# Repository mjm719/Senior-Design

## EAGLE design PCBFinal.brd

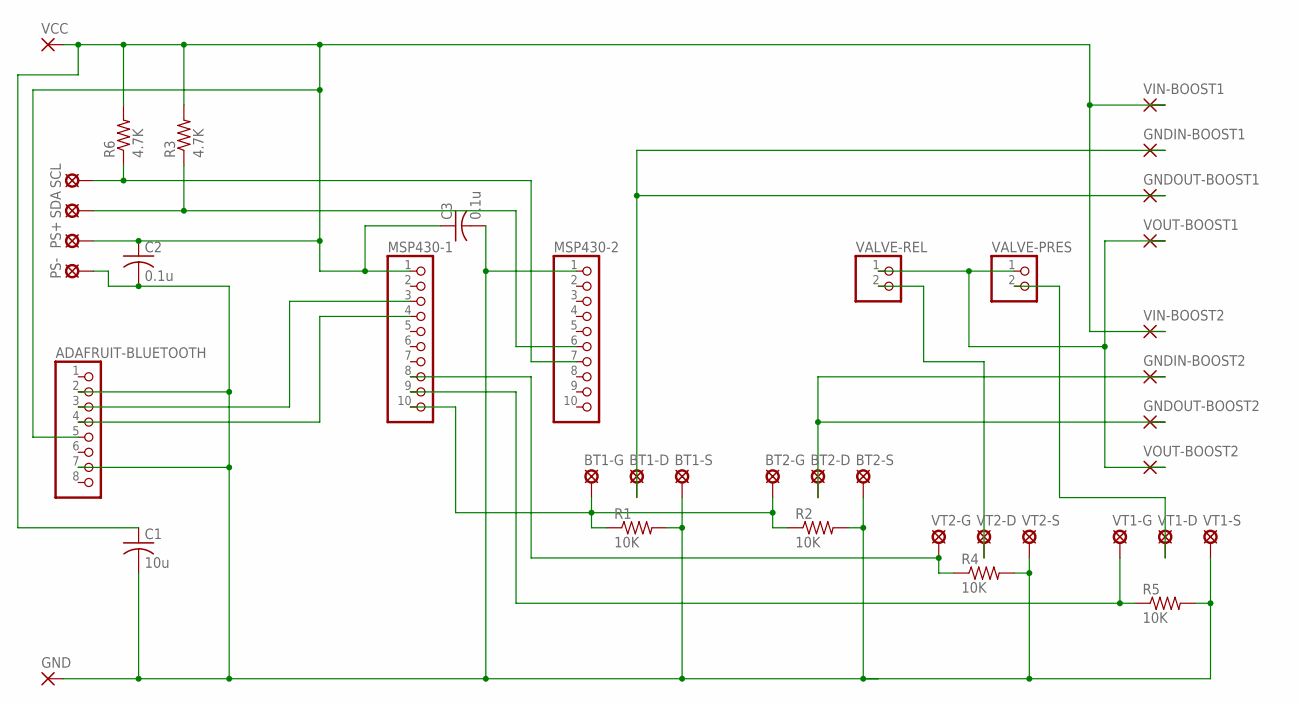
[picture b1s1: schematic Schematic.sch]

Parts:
ADAFRUIT-BLUETOOTH: PINHD-1X8; 1X08
BT1-D, BT1-G, BT1-S, BT2-D, BT2-G, BT2-S: LSP10
C1: 10u; C0805
C2, C3: 0.1u; C0805
GND: SMD5; SMD2,54-5,08
GNDIN-BOOST1, GNDIN-BOOST2: SMD5; SMD2,54-5,08
GNDOUT-BOOST1, GNDOUT-BOOST2: SMD5; SMD2,54-5,08
MSP430-1, MSP430-2: PINHD-1X10; 1X10
PS+: LSP10
PS-: LSP10
R1, R2, R4, R5: 10K; 0309/12
R3, R6: 4.7K; 0309/12
SCL: LSP10
SDA: LSP10
VALVE-PRES: PINHD-1X2; 1X02
VALVE-REL: PINHD-1X2; 1X02
VCC: SMD5; SMD2,54-5,08
VIN-BOOST1, VIN-BOOST2: SMD5; SMD2,54-5,08
VOUT-BOOST1, VOUT-BOOST2: SMD5; SMD2,54-5,08
VT1-D, VT1-G, VT1-S, VT2-D, VT2-G, VT2-S: LSP10

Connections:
unnamed: MSP430-2.7, R6.1, SCL.MP
unnamed: MSP430-2.6, R3.1, SDA.MP
unnamed 2: ADAFRUIT-BLUETOOTH.5, C1.1, C2.1, C3.1, MSP430-1.1, PS+.MP, R3.2, R6.2, VCC.1, VIN-BOOST1.1, VIN-BOOST2.1; also elsewhere on the board
unnamed: ADAFRUIT-BLUETOOTH.3, MSP430-1.3
unnamed: ADAFRUIT-BLUETOOTH.4, MSP430-1.4
unnamed: VALVE-PRES.1, VALVE-REL.1, VOUT-BOOST1.1, VOUT-BOOST2.1
unnamed 6: ADAFRUIT-BLUETOOTH.2, ADAFRUIT-BLUETOOTH.7, BT1-S.MP, BT2-S.MP, C1.2, C2.2, C3.2, GND.1, MSP430-2.1, PS-.MP, R1.2, R2.2, R4.2, R5.2, VT1-S.MP, VT2-S.MP; also elsewhere on the board
unnamed: MSP430-1.8, R4.1, VT2-G.MP
unnamed: BT1-G.MP, BT2-G.MP, MSP430-1.10, R1.1, R2.1
unnamed: MSP430-1.9, R5.1, VT1-G.MP
unnamed: VALVE-PRES.2, VT1-D.MP
unnamed: VALVE-REL.2, VT2-D.MP
unnamed: BT1-D.MP, GNDIN-BOOST1.1, GNDOUT-BOOST1.1
unnamed: BT2-D.MP, GNDIN-BOOST2.1, GNDOUT-BOOST2.1

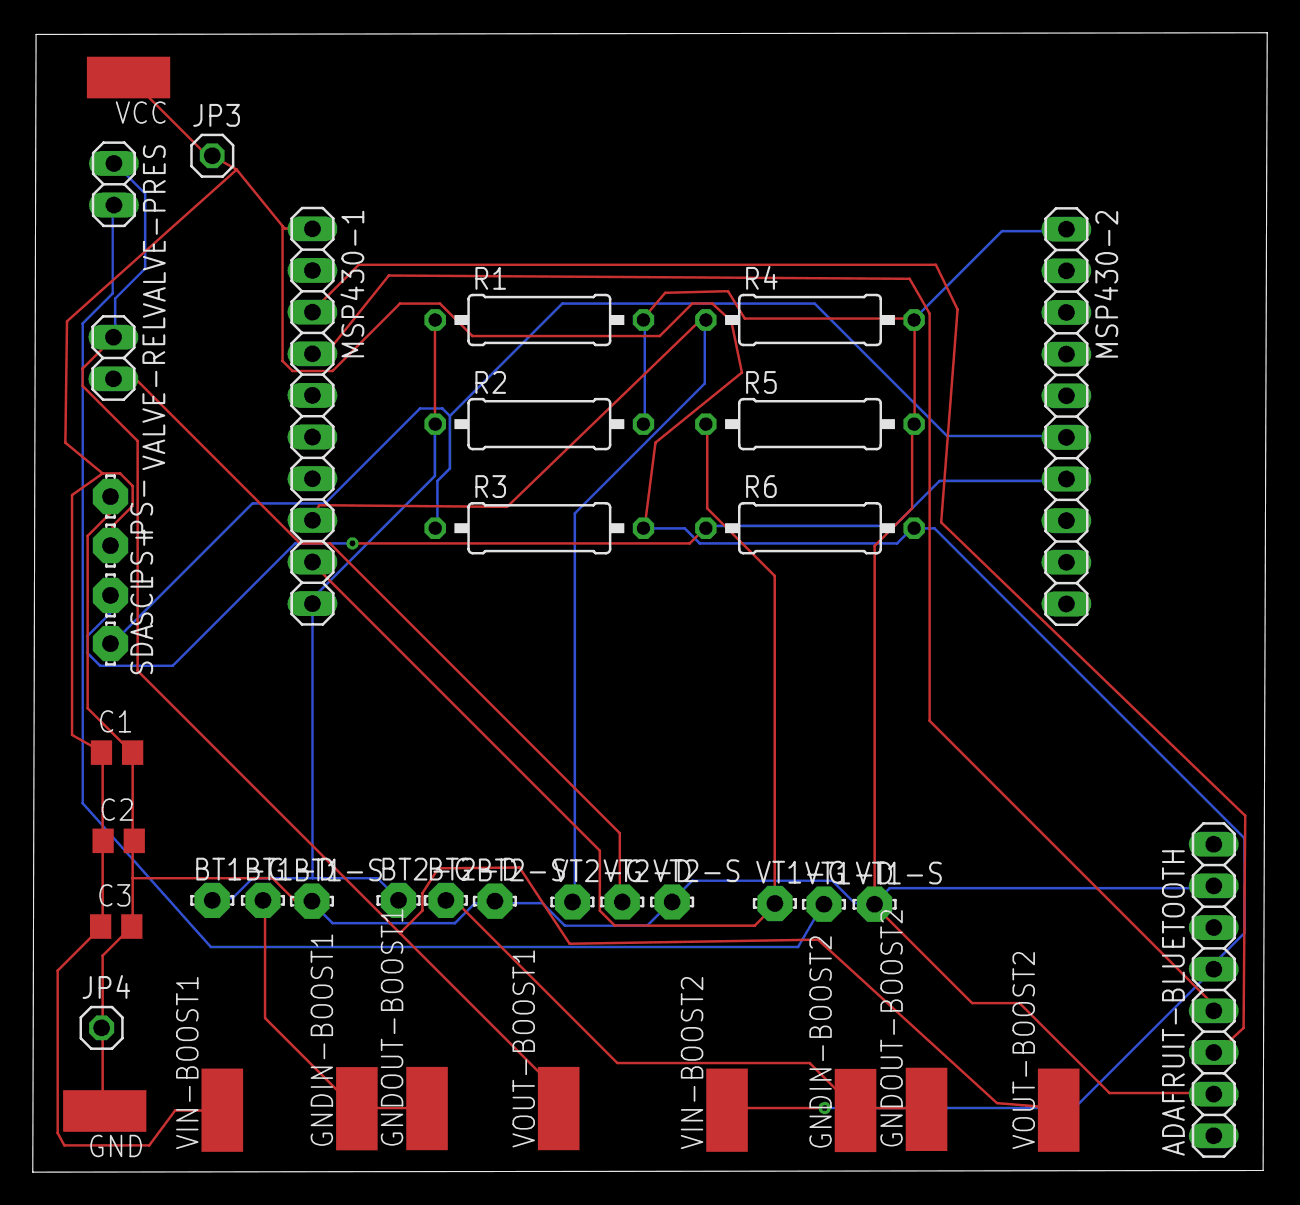
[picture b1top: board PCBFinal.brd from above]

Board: 2 copper layers, 75.3 x 69.5 mm, 42 parts (0 on the bottom side), 14 nets.

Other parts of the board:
JP3, JP4: 1X01

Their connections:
unnamed 2: JP3.1; also elsewhere on the board
unnamed 6: JP4.1; also elsewhere on the board

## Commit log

2016-12-15 Uploading Sample Code
    Creating Initial Folders
2016-12-15 MSP430 Document
    Extremely Useful document. Explains how to program the MSP430
2016-12-15 Document with Parts
    Not even close to finished. Just ideas I have for parts
2016-12-21 Adding MSP430 Pinout
    Not all will be connected. Excel sheet show on the microcontroller tab
    what our connections need to be
2016-12-21 Document for Bluetooth Specs
2016-12-21 Update
    Has link to battery I posted. Just to keep track of it so we don't lose
    it
2017-02-08 Parts Update
    Also Contains a few miscellaneous things
2017-02-13 Order Info
2017-03-04 Adding base case, working uart program for cc2650
2017-03-04 moving base case, working uart program for cc2650 to appropriate folder
2017-03-04 moved cc2650 uart code to bluetooth code folder
2017-03-04 New Order
2017-03-04 More Order Forms
2017-03-04 Working UART code
    Also has beginnings of the main program to be used
2017-03-08 adding test multi-byte uart
2017-03-08 Even More Part Orders
    $$$$$$$$
2017-03-09 MSP430 Code
    UART, Multi-Byte UART, I2C
2017-03-09 adding functional uart echo multi byte for cc2650
2017-03-29 Add files via upload
    Android Bluetooth Connectivity Source Code
2017-03-29 Rename MainActivity.cs to Android/BluetoothTestingv2/MainActivity.c
2017-03-29 Rename Android/BluetoothTestingv2/MainActivity.cs to Android/BPR/MainActivity.cs
2017-03-29 Rename Android/BluetoothTestingv2/MainActivity.c to Android/Bluetooth/MainActivity.cs
2017-03-29 Rename Android/BPR/MainActivity.cs to Android/Main/MainActivity.cs
2017-03-29 cleanup
2017-03-30 added bluetooth and main
2017-03-30 various cleanup
2017-03-30 added LE project
2017-03-31 BLE update
2017-03-31 added GATT connection
2017-04-01 Bluetooth Java Code
2017-04-03 update 4/3/17
2017-04-03 adding Project Zero (bluetooth example)
2017-04-03 Adding Project Zero stack
2017-04-03 adding Multibyte UART project
2017-04-03 added GATT server connection
2017-04-05 added permissions request at runtime
2017-04-06 added BLE characteristic read functionality
2017-04-06 added high level read/write functions
2017-04-06 various cleanup; added button control
2017-04-06 successful read/write operation implemented
2017-04-09 integrated BluetoothLE into Main app
2017-04-11 adding project zero that can read consistently and write once
2017-04-11 Parts Order and Pressure Accuracy Table
2017-04-11 Code - UART_I2C should be main
    I need to rename the files, but UART_I2C.c is what currently has almost
    all of the code implemented together
2017-04-11 pushing project zero
2017-04-11 adding project zero that can read continously but only write new data once
2017-04-15 added button disabling during pressure changes
2017-04-15 added loading screen
2017-04-17 added loading bar
2017-04-20 New Parts and Pressure Table
2017-04-20 Code for BPR
    Most functionaility is commented out. Will upload a new version when
    pressure sensor comes in
2017-04-20 modified characteristics for Adafruit module
2017-04-21 added force idle button
2017-04-22 if it aint broke, dont fix it
2017-04-22 MSP430 Code - THIS WORKS!!!!!!!!
2017-04-25 Newer Version of Main Code
2017-04-25 semeseter 1 demo
2017-04-27 Created Parts Order Folder
2017-04-27 Adding Data Sheets for Parts
2017-04-27 Moving Files to Folders for Ease of Finding
2017-04-27 Removing Files that were never used
2017-04-30 Removing now unecessary folder for Bluetooth code.
2017-05-01 Schematic Upload
    Also has testing for pressure control
2017-05-01 Removing Extra Folder
2017-05-02 Version 1.00: Senior Design I Base Application Prototype
2017-05-03 More Data Sheets
2017-05-03 Schematic
2017-11-27 Remove Useless Schematic
2017-11-27 Upload Schematic and PCB file
2017-11-28 Packaging
